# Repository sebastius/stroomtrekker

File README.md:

# stroomtrekker
Clone of Pwuts' Metertrekker project (https://gitlab.com/Pwuts/Metertrekker). Stroomtrekker/Metertrekker is a tiny circuit to read the status of your power consumption meter via the P1 port. Both our versions should be able to power an ESP8266/32 via the P1 port, so no extra cables required! You can then use the microcontroller to publish the acquired data over MQTT or any other protocol, should you choose to write software for it ;)

Boards have *just* been ordered, so make these at your own risk.

## BOM
### Semiconductors
* 1x Wemos D1 mini or ESP32 D1 mini
* 1x 2N7002 mosfet (or any generic SOT23 mosfet will probably work)

### Resistors
(all 0805 size)
* 1x 470R
* 1x 2K4
* 1x 4K8

### Capacitors
* 1x 470uF 6.3V

### Connectors and cables
* 1x RJ12 connector
* 1x RJ12 cable

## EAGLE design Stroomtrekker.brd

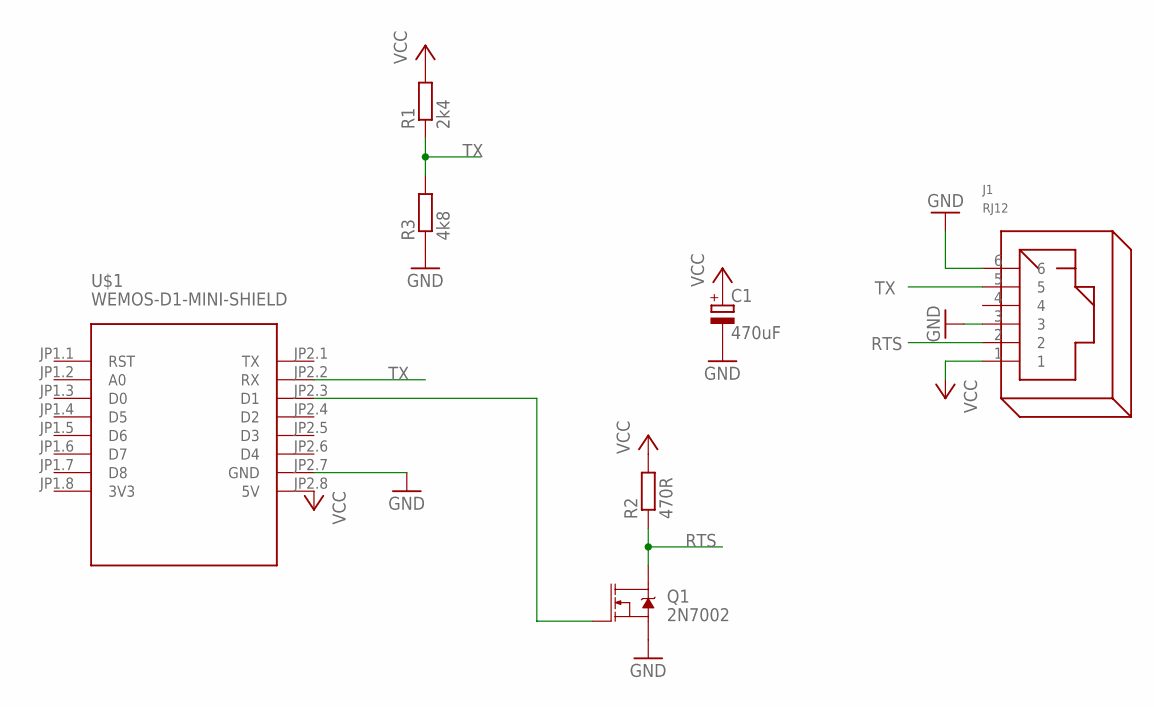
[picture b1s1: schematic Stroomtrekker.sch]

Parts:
C1: 470uF; E2,5-6
J1: RJ12
Q1: 2N7002; SOT323
R1: 2k4; R0805
R2: 470R; R0805
R3: 4k8; R0805
U$1: WEMOS-D1-MINI-SHIELD

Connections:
3V3: U$1.JP1.8 (3V3)
GND: C1.-, J1.3, J1.6, Q1.2 (S), R3.1, U$1.JP2.7 (GND)
unnamed: Q1.1 (G), U$1.JP2.3 (D1)
RTS: J1.2, Q1.3 (D), R2.1
TX: J1.5, R1.1, R3.2, U$1.JP2.2 (RX)
VCC: C1.+, J1.1, R1.2, R2.2, U$1.JP2.8 (5V)

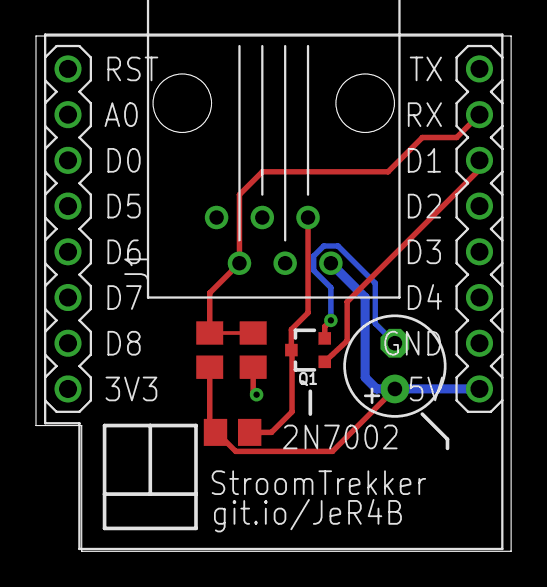
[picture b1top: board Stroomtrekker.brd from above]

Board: 2 copper layers, 26.4 x 28.6 mm, 7 parts (0 on the bottom side), 5 nets.

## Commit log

2019-10-22 Eerste versie
    Eagle 9.5, incl gerbers
2019-10-22 Picture!

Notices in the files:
parts and their libraries:
SparkFun-DiscreteSemi: Licensing: Creative Commons ShareAlike 4.0 International - https://creativecommons.org/licenses/by-sa/4.0
diy-modules: Released under the Creative Commons Attribution 4.0 International License: http://creativecommons.org/licenses/by/4.0
